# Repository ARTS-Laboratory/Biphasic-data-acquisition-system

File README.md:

# Biphasic-data-acquisition-system
Data acquisition system for the biphasic measurement of multifunctional materials. The measurement method is described in by Downey et al [1], while the initial layout of the hardware was developed by Hasan Borke Birgin at the University of Perugia. Figure 1 shows an overview of the bi-phasic measurement approach. 

<p align="center">
Figure 2: The Biphasic DC measurement approach, showing: (left) electrical signals of a 1 Hz square wave: sensing current with 50% duty cycle showing the discharge and measure regions, as well as the sample points for the applied and sense voltages, and; (right) time-based comparison of traditional DC resistance and the proposed biphasic DC measurement method using a 50% duty cycle and 9 varying sensing current frequencies, annotated on the right-hand side of the figure. 
</p>

[1] Austin Downey, Antonella D'Alessandro, Filippo Ubertini, Simon Laflamme and Randall Geiger. Biphasic DC Measurement Approach for Enhanced Measurement Stability and Multi-channel Sampling of Self-sensing Multi-functional Structural Materials Doped With Carbon-based Additives. Smart Materials and Structures, vol. 26, no. 6, 2017, p. 065008. doi:10.1088/1361-665X/aa6b66

## DAQ Design
1. This contains the hardware design and code for the DAQ system
1. Orginized by versions

## Licensing and Citation

[![CC BY-SA 4.0][cc-by-sa-shield]][cc-by-sa]

This work is licensed under a
[Creative Commons Attribution-ShareAlike 4.0 International License][cc-by-sa].

[cc-by-sa]: http://creativecommons.org/licenses/by-sa/4.0/
[cc-by-sa-image]: https://licensebuttons.net/l/by-sa/4.0/88x31.png
[cc-by-sa-shield]: https://img.shields.io/badge/License-CC%20BY--SA%204.0-lightgrey.svg

Cite as:

ARTS-Lab. Biphasic data acquisition system. GitHub. URL: https://github.com/ARTS-Laboratory/Biphasic-data-acquisition-system
 
in bibtex

@Misc{ARTSLabBiphasicDataAcquisition,   
  author       = {{ARTS-L}ab},  
  howpublished = {GitHub},  
  title        = {Biphasic Data Acquisition System},   
  groups       = {{ARTS-L}ab},  
  url          = {https://github.com/ARTS-Laboratory/Biphasic-data-acquisition-system},  
  note  = {Accessed: Month dd, yyyy},   
}

<p align="center">
QR code for repo.
</p>

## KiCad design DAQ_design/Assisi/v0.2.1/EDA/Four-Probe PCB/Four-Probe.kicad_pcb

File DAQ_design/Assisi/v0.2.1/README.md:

# Assisi V0.2.1

* This uses kicad-9.0.5 -->  https://downloads.kicad.org/kicad/windows/explore/stable/download/kicad-9.0.5-x86_64.exe
* Use a NI-9221 with a DSUB 25 female 
	* https://www.digikey.com/en/products/detail/amphenol-cs-fci/D25S33E4PA00LF/1538080
	* https://www.digikey.com/en/products/detail/edac-inc/630-025-640-541/10867386

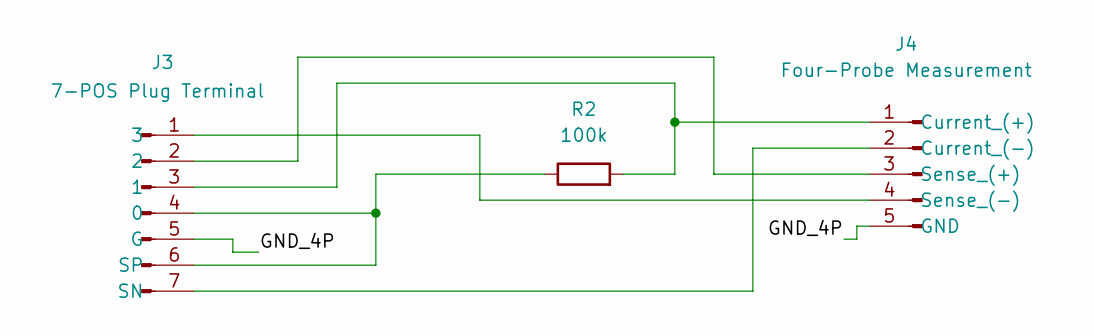
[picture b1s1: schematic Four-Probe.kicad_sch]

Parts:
J3: 7-POS Plug Terminal; PHOENIX_1786459
J4: Four-Probe Measurement; PhoenixContact_MSTBA_2,5_5-G-5,08_1x05_P5.08mm_Horizontal
R2: 100k; R_Axial_DIN0207_L6.3mm_D2.5mm_P10.16mm_Horizontal

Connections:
/GND_4P: J3.5 (G), J4.5 (GND)
unnamed: J3.4 (0), J3.6 (SP), R2.1
unnamed: J3.3 (1), J4.1 (Current_(+)), R2.2
unnamed: J3.1 (3), J4.4 (Sense_(-))
unnamed: J3.7 (SN), J4.2 (Current_(-))
unnamed: J3.2, J4.3 (Sense_(+))

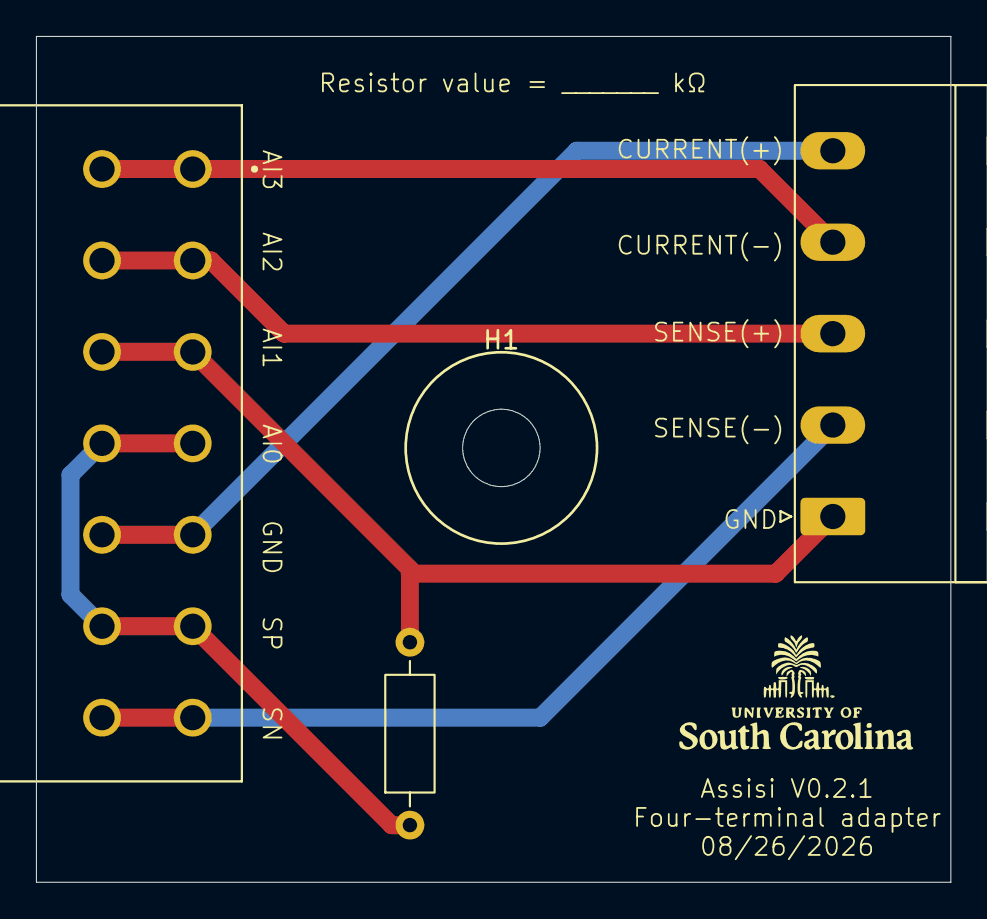
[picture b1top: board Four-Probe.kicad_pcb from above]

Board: 2 copper layers, 50.8 x 47.0 mm, 5 parts (0 on the bottom side), 6 nets.

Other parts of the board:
G2: LOGO; uofsc
H1: MountingHole_Pad; MountingHole_4.3mm_M4

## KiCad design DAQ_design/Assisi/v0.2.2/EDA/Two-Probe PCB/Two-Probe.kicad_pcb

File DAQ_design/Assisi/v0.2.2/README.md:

# Assisi V0.2.2

* This uses kicad-9.0.5 -->  https://downloads.kicad.org/kicad/windows/explore/stable/download/kicad-9.0.5-x86_64.exe
* Update from PCB version 0.2.1 to 0.2.2.
* Add a notch/cutout in the PCB so the board fits in the enclosure more cleanly.
* Shorten the PCB slightly to reduce package size.
* Continue using external power supplies.
* Target 9 V external power as the preferred operating supply.
* Explore 7 V external power as an alternate option.
* Clean up the PCB schematic for readability and consistency.
* Clean up PCB traces and routing.
* Update the enclosure mounting pattern from three holes to two holes.

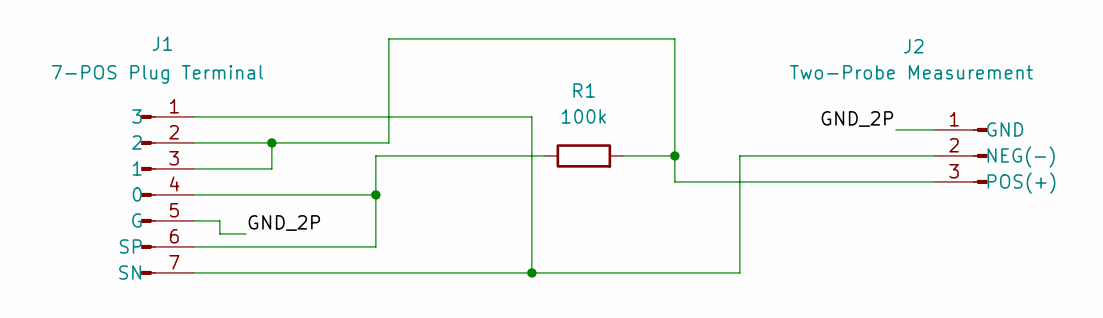
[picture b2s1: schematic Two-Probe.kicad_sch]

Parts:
J1: 7-POS Plug Terminal; PHOENIX_1786459
J2: Two-Probe Measurement; PhoenixContact_MSTBA_2,5_3-G-5,08_1x03_P5.08mm_Horizontal
R1: 100k; R_Axial_DIN0207_L6.3mm_D2.5mm_P10.16mm_Horizontal

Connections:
/GND_2P: J1.5 (G), J2.1 (GND)
unnamed: J1.4 (0), J1.6 (SP), R1.1
unnamed: J1.2, J1.3 (1), J2.3 (POS(+)), R1.2
unnamed: J1.1 (3), J1.7 (SN), J2.2 (NEG(-))

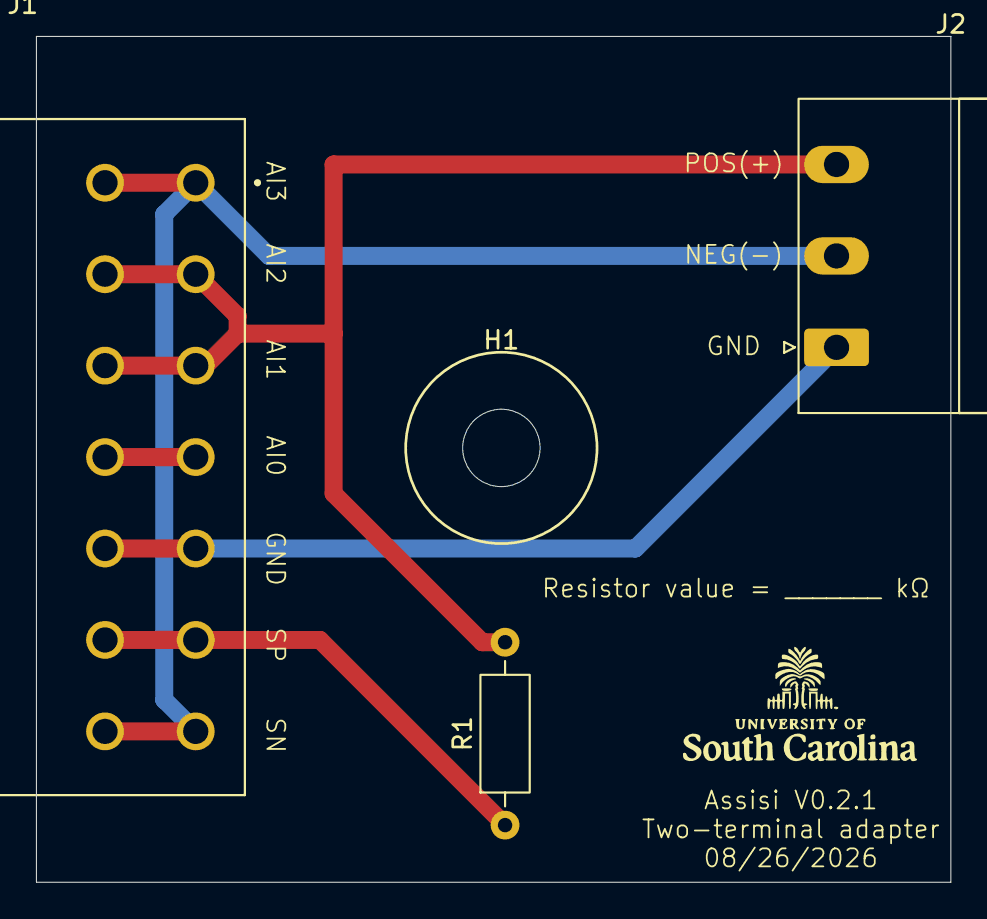
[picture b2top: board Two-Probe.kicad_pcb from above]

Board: 2 copper layers, 50.8 x 47.0 mm, 5 parts (0 on the bottom side), 4 nets.

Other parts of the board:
G2: LOGO; uofsc
H1: MountingHole_Pad; MountingHole_4.3mm_M4

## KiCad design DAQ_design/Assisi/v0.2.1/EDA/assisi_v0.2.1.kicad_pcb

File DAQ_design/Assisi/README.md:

# Assisi
* Biphasic DAQ with ADC done cDAQ hardware

## V0.1.0
* Initial Assisi PCB version copied forward from earlier circuitry.
* Used as a holdover design to preserve and test the core circuit layout.

## V0.2.0
* First version focused on adapting the DAQ PCB for the enclosure.
* Began moving the design toward a boxed, deployable hardware package.

## V0.2.1
* Fixed issues found in V0.2.0 and added enclosure bolt holes.
* Printed enclosure version sent to Italy in June 2026.

## V0.2.2
* Shortened the PCB and added a notch/cutout for better enclosure fit.
* Cleaned up the schematic, PCB traces, and moved to two mounting holes.

## V0.2.3
* Future version to explore direct 5 V power input without the Arduino regulator.
* Planned update to include integrated resistor management.

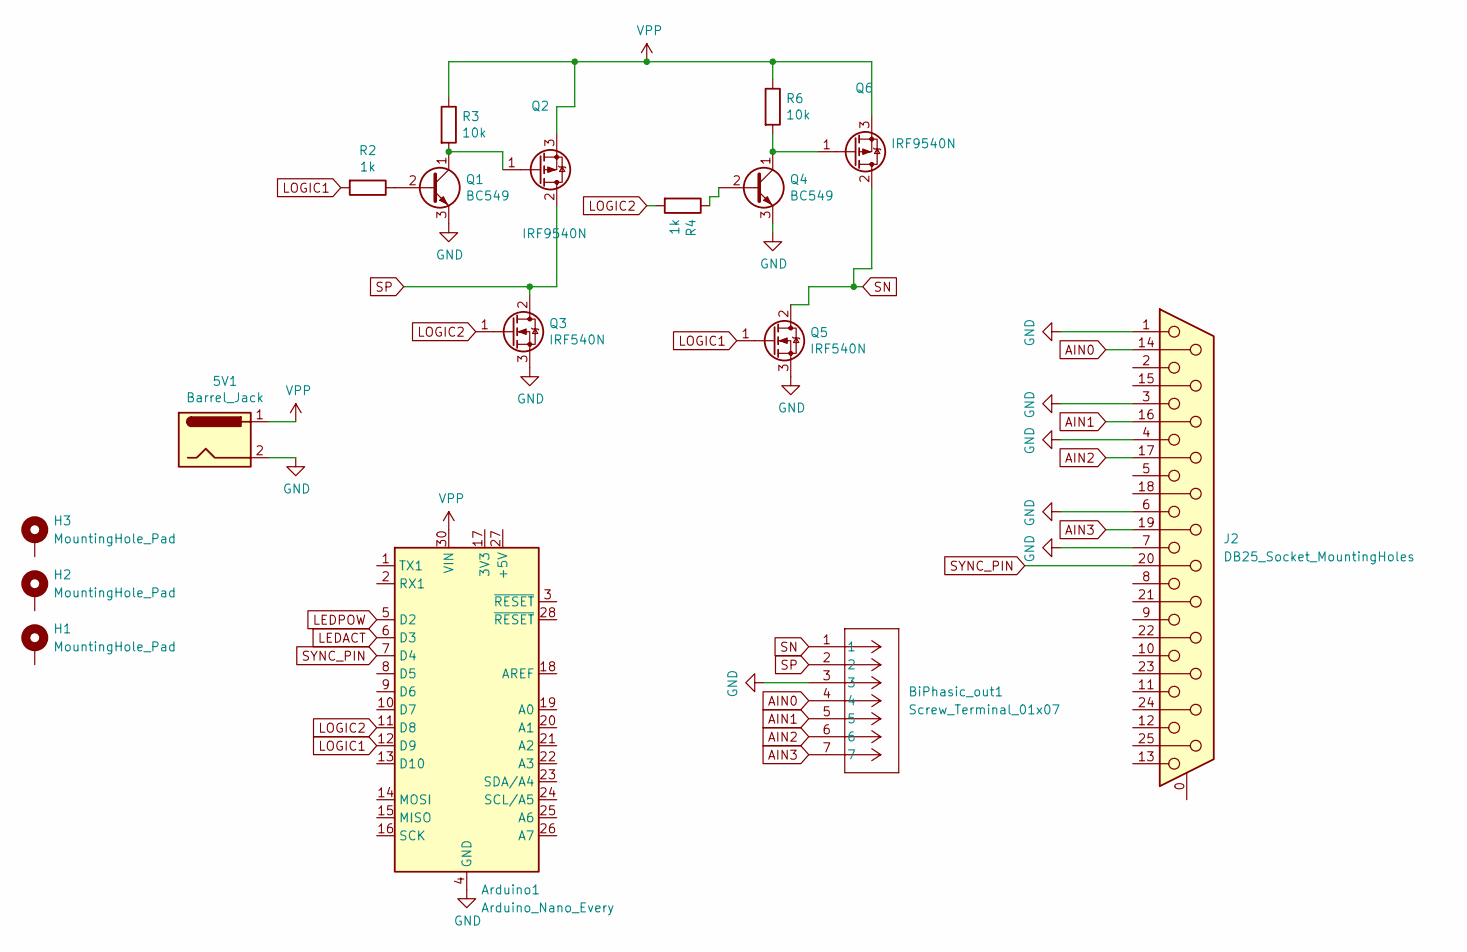
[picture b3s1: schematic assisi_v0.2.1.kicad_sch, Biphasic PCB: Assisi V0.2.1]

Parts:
5V1: Barrel_Jack; BarrelJack_Horizontal
Arduino1: Arduino_Nano_Every; Arduino_Nano
BiPhasic_out1: Screw_Terminal_01x07; CONN7_57297_PXC
H1, H2, H3: MountingHole_Pad; MountingHole_4.3mm_M4
J2: DB25_Socket_MountingHoles; DSUB-25_Pins_Horizontal_P2.77x2.84mm_EdgePinOffset7.70mm_Ho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
Q1, Q4: BC549; TO-92_Inline_Wide
Q2, Q6: IRF9540N; TO-220-3_Vertical
Q3, Q5: IRF540N; TO-220-3_Vertical
R2, R4: 1k; R_1206_3216Metric
R3, R6: 10k; R_1206_3216Metric

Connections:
AIN0: BiPhasic_out1.4, J2.14
AIN1: BiPhasic_out1.5, J2.16
AIN2: BiPhasic_out1.6, J2.17
AIN3: BiPhasic_out1.7, J2.19
GND: 5V1.2, Arduino1.4 (GND), Arduino1.29 (GND), BiPhasic_out1.3, J2.1, J2.3, J2.4, J2.6, J2.7, Q1.3 (E), Q3.3 (S), Q4.3 (E), Q5.3 (S); also elsewhere on the board
LEDACT: Arduino1.6 (D3)
LEDPOW: Arduino1.5 (D2)
LOGIC1: Arduino1.12 (D9), Q5.1 (G), R2.2
LOGIC2: Arduino1.11 (D8), Q3.1 (G), R4.2
unnamed: Q1.2 (B), R2.1
unnamed: Q1.1 (C), Q2.1 (G), R3.2
unnamed: Q4.2 (B), R4.1
unnamed: Q4.1 (C), Q6.1 (G), R6.2
SN: BiPhasic_out1.1, Q5.2 (D), Q6.2 (D)
SP: BiPhasic_out1.2, Q2.2 (D), Q3.2 (D)
SYNC_PIN: Arduino1.7 (D4), J2.20
VPP: 5V1.1, Arduino1.30 (VIN), Q2.3 (S), Q6.3 (S), R3.1, R6.1; also elsewhere on the board

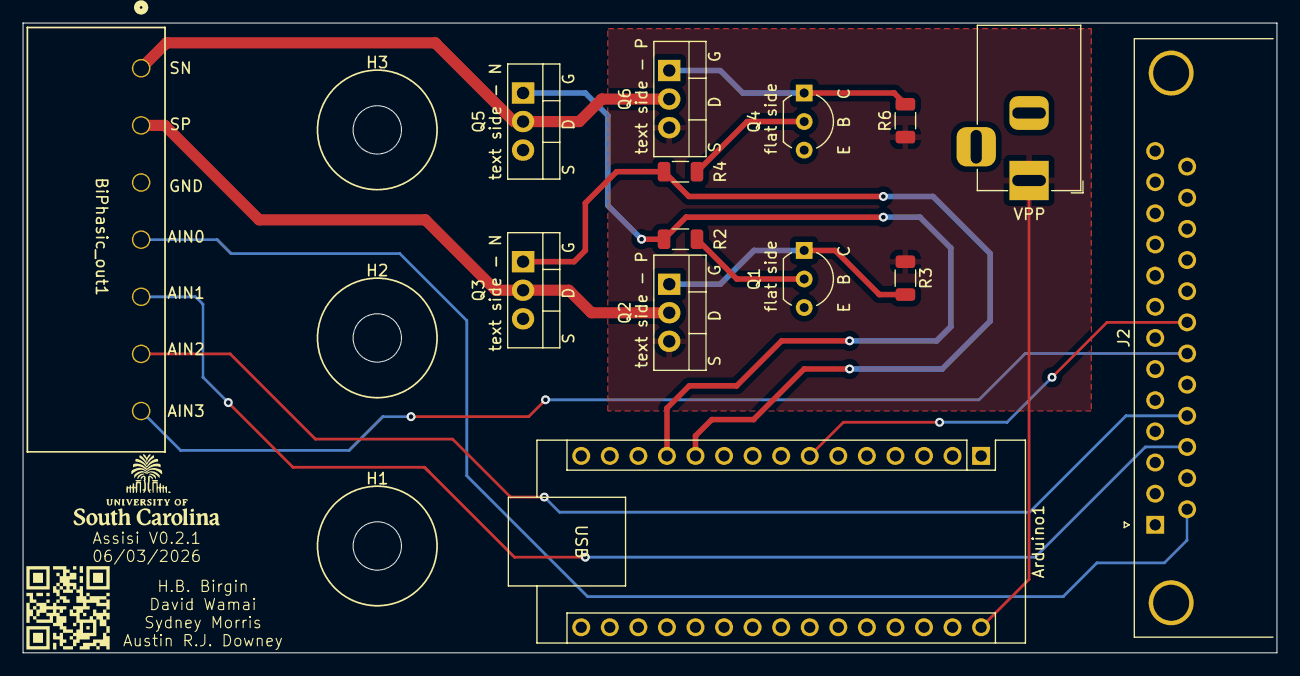
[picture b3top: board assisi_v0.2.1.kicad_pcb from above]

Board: 2 copper layers, 111.5 x 56.0 mm, 19 parts (0 on the bottom side), 15 nets.

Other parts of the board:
G2: LOGO; uofsc
G7: LOGO; github
VPP: Barrel_Jack; BarrelJack_Horizontal

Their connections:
GND: VPP.2; also elsewhere on the board
VPP: VPP.1; also elsewhere on the board

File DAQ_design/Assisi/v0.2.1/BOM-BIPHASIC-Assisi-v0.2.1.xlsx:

Designator | Component | MFR Part Number | Amount in Inventory | Amount Per Board | Individual Cost | Total Cost | Notes | Vendor 1 | Vendor 2 | Vendor 3 | Vendor 4 | Vendor 5 | Vendor 6
VPP | Barrel Jack | PJ-002A | 6 | 1 | 0.57999999999999996 | 0.57999999999999996 |  | PJ-002A Same Sky (Formerly CUI Devices) | Power Connectors | DigiKey
Arduino1 | Arduino Nano Microcontroller |  | 0 | 1 | 5.9 | 5.9 | Can be swapped with a nano every for a higher ram option | https://www.digikey.com/en/products/detail/dfrobot/DFR0010/6588448
BiPhasic_out1 | Screw Terminal Male | 1757064 | 2 | 1 | 4.72 | 4.72 | Allow for secure yet detachable wiring | 1757297 Phoenix Contact | Headers, Plugs and Sockets | DigiKey
BiPhasic_out1 | Screw Terminal Female | 1757297 | 7 | 1 | 12.55 | 12.55 | Allow for secure yet detachable wiring | 1757064 Phoenix Contact | Headers, Plugs and Sockets | DigiKey
BiPhasic_out1 | Screw Terminal Female with strain relief | 1776113 | 2 | 1 | 9.5 | 9.5 | Allow for secure yet detachable wiring (with strain relief) | https://www.digikey.com/en/products/detail/phoenix-contact/1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
J2 DSUB | DSUB-25 Female Connector | D25S33E4GX00LF | 3 | 1 | 1.81 | 1.81 | Connect to NI 9221 | https://www.digikey.com/en/products/detail/amphenol-cs-fci/D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
R2, R4 | 1k Ohm Resistor | RC1206FR-071KL | 42 | 2 | 0.1 | 0.2 | Or use resistor book: https://www.adafruit.com/product/441 | RC1206FR-071KL YAGEO | Chip Resistor - Surface Mount | DigiKey
R3, R6 | 10k Ohm Resistor | RMCF1206FT10K0 | 42 | 2 | 0.1 | 0.2 | Or use resistor book: https://www.adafruit.com/product/442 | RMCF1206FT10K0 Stackpole Electronics Inc | Chip Resistor - Surface Mount | Digi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
Q1, Q4 | Epitaxial Silicon Transistor | BC550CTA | 4 | 2 | 0.28000000000000003 | 0.56000000000000005 | CTA is higher-gain, low-noise | BC550CTA onsemi | Single Bipolar Transistors | DigiKey
Q2, Q6 | HEXFET power MOSFET | IRF9540NPBF | 0 | 2 | 2.0699999999999998 | 4.1399999999999997 | Need both for complementary pair. P-channel (when gate is lower than source, pu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 | IRF9540NPBF Infineon Technologies | Single FETs, MOSFETs | DigiKey
Q3, Q5 | IRF540N HEXFET power MOSFET |  | 6 | 2 | 1.93 | 3.86 | Need both for complementary pair. N-channel (when gate is higher than source, p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 | IRF540NPBF Infineon Technologies | Single FETs, MOSFETs | DigiKey
H1, H2, H3 | M4 Flat Washer | M51420.040.0001 | 60 | 9 | 1.66E-2 | 0.14940000000000001 | Package quantity 50 | https://www.grainger.com/product/Flat-Washer-18-8-26WC32
 | M4 x 40 mm Socket Head Cap Screw | 6DB37 | 32 | 6 | 0.20620000000000002 | 1.2372000000000001 | Package quantity 50. secures box lid to bottom | https://www.grainger.com/product/Socket-Head-Cap-Screw-M4x0-6DB37
 | M4 x 16 mm Socket Head Cap Screw | 22UC47 | 41 | 3 | 0.11800000000000001 | 0.35400000000000004 | Package quantity 50. secures PCB to box bottom | https://www.grainger.com/product/Socket-Head-Cap-Screw-M4x0-22UC47
 | M4 Hex Nut | M51080.040.0001 | 60 | 9 | 1.54E-2 | 0.1386 | Package quantity 50 | https://www.grainger.com/product/Hex-Nut-Std-Hex-22UK82
 | DSUB Screw | 5746879-1 | 10 | 2 | 0.59 | 1.18 |  | 5746879-1 TE Connectivity AMP Connectors | D-Sub, D-Shaped Connector Jackscrews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
 | 15 Pos Female Header Pins |  | 0 | 2 | 5.86 | 11.72 | Solder to microcontroller footprint to make detachable | 1-215297-5 TE Connectivity AMP Connectors | Headers, Receptacles, Female Socket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
 | Power Supply 9V |  | 1 | 1 | 18.600000000000001 | 18.600000000000001 | Convenient and plugs into wall | GST60A12-P1J MEAN WELL USA Inc. | AC DC Desktop, Wall Power Adapters | DigiKey
 | Power Supply 12V |  | 3 | 1 | 18.600000000000001 | 18.600000000000001 | Convenient and plugs into wall | https://www.digikey.com/en/products/detail/mean-well-usa-inc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
 | hook up wire | 76502.18.01 | 1 | 1 | 65.510000000000005 | 65.510000000000005 | 500' of 18 AWG 16/30 hook-up wire, black, will be color-coded with crimp termin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 | https://www.digikey.com/en/products/detail/encore-wire/76502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
 | Ferrule - gray | 3200519 | 25 | 2 | 0.15 | 0.3 | Color coded Ferrule to go with the black wire | https://www.digikey.com/en/products/detail/phoenix-contact/3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
 | Ferrule - yellow | 3201097 | 21 | 2 | 0.15 | 0.3 | Color coded Ferrule to go with the black wire | https://www.digikey.com/en/products/detail/phoenix-contact/3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
 | Ferrule - white | 3201110 | 25 | 2 | 0.15 | 0.3 | Color coded Ferrule to go with the black wire | https://www.digikey.com/en/products/detail/phoenix-contact/3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
 | Ferrule - red | 3200904 | 25 | 2 | 0.15 | 0.3 | Color coded Ferrule to go with the black wire | https://www.digikey.com/en/products/detail/phoenix-contact/3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
wire to mesh connector | Barrier Terminal Strip | 6YH99 |  | 1 | 0.45083333333333336 | 0.45083333333333336 | Cut apart and use to connect to wire mesh in concrete | https://www.grainger.com/product/Barrier-Terminal-Strip-12-6YH99
 | cDAQ NI 9221 with DSUB | NI 9221 779373-01 | 3 | 1 | 1220 | 1220 |  | NI-9221 - NI
 | cDAQ Chassis NI 9171 | NI 9171 781425-01 | 3 | 1 | 548 | 548
 |  |  |  |  | Total | 1931.1600333333333

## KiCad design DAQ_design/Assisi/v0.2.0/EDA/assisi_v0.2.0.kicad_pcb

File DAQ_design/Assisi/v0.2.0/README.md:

# Assisi V0.2.0

* This uses kicad-9.0.5 -->  https://downloads.kicad.org/kicad/windows/explore/stable/download/kicad-9.0.5-x86_64.exe
* Use a NI-9221 wiht a DSUB 25 female 
	* https://www.digikey.com/en/products/detail/amphenol-cs-fci/D25S33E4PA00LF/1538080
	* https://www.digikey.com/en/products/detail/edac-inc/630-025-640-541/10867386

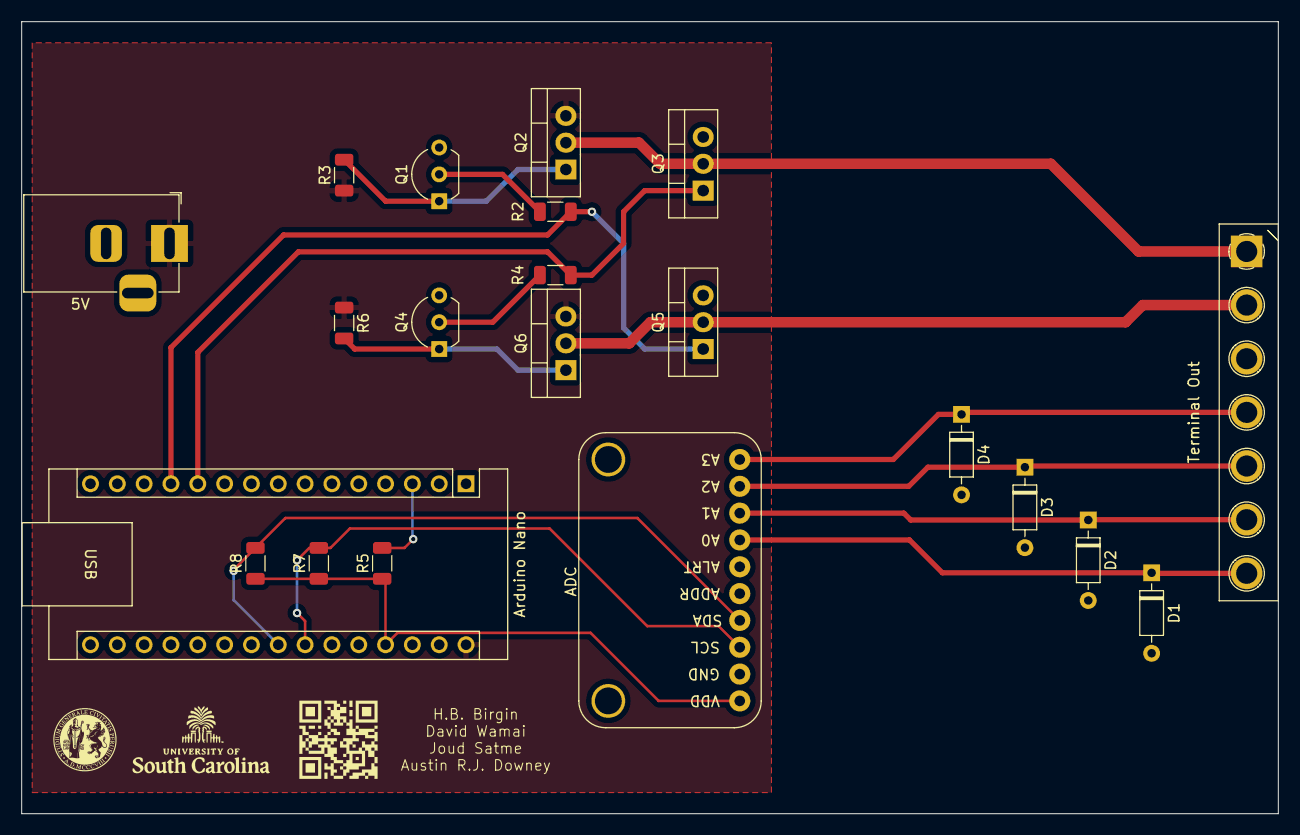
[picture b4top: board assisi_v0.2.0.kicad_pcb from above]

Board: 2 copper layers, 119.0 x 75.0 mm, 25 parts (1 on the bottom side), 18 nets.

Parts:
5V: Barrel_Jack; BarrelJack_Horizontal
ADC: ADS1115IDGS; Adafruit_ADS1115
Arduino Nano: Arduino_Nano_Every; Arduino_Nano
D1, D2, D3, D4: D_Zener; D_DO-35_SOD27_P7.62mm_Horizontal
G2: LOGO; uofsc
G3: LOGO; upg
G5: LOGO; schematic
G7: LOGO; github
Q1, Q4: BC549; TO-92_Inline_Wide
Q2, Q6: IRF9540N; TO-220-3_Vertical
Q3, Q5: IRF540N; TO-220-3_Vertical
R2, R4: 1k; R_1206_3216Metric
R3, R5, R6, R7, R8: 10k; R_1206_3216Metric
Terminal Out: Screw_Terminal_01x07; TerminalBlock_Phoenix_MKDS-1,5-7-5.08_1x07_P5.08mm_Horizont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

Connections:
AIN0: ADC.7 (AIN0), D1.1 (K), Terminal Out.7
AIN1: ADC.8 (AIN1), D2.1 (K), Terminal Out.6
AIN2: ADC.9 (AIN2), D3.1 (K), Terminal Out.5
AIN3: ADC.10 (AIN3), D4.1 (K), Terminal Out.4
GND: 5V.2, ADC.2 (GND), ADC.5 (ADDR), Arduino Nano.4 (GND), Arduino Nano.29 (GND), D1.2 (A), D2.2 (A), D3.2 (A), D4.2 (A), Q1.3 (E), Q3.3 (S), Q4.3 (E), Q5.3 (S), Terminal Out.3
LOGIC1: Arduino Nano.12 (D9), Q5.1 (G), R2.2
LOGIC2: Arduino Nano.11 (D8), Q3.1 (G), R4.2
unnamed: ADC.3 (SCL), Arduino Nano.24 (SCL/A5), R7.2
unnamed: ADC.4 (SDA), Arduino Nano.23 (SDA/A4), R8.2
unnamed: Arduino Nano.3 (~RESET), R5.2
unnamed: Q1.2 (B), R2.1
unnamed: Q1.1 (C), Q2.1 (G), R3.2
unnamed: Q4.2 (B), R4.1
unnamed: Q4.1 (C), Q6.1 (G), R6.2
SN: Q5.2 (D), Q6.2 (D), Terminal Out.2
SP: Q2.2 (D), Q3.2 (D), Terminal Out.1
VDD: ADC.1 (VDD), Arduino Nano.27 (+5V), R5.1, R7.1, R8.1
VPP: 5V.1, Arduino Nano.30 (VIN), Q2.3 (S), Q6.3 (S), R3.1, R6.1

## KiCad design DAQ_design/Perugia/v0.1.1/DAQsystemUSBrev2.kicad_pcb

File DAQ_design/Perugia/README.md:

# Perugia
* Biphasic DAQ with ADC done on an embedded microcontroller

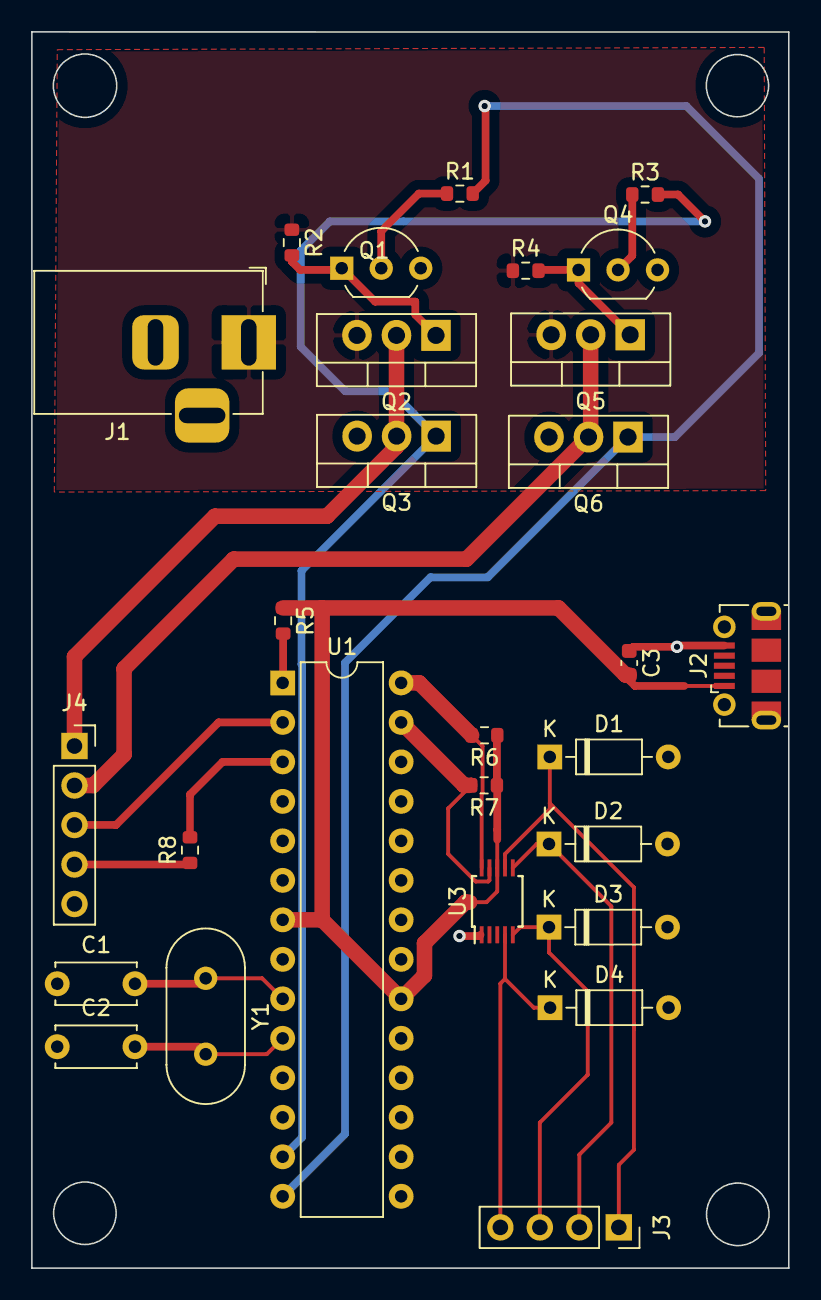
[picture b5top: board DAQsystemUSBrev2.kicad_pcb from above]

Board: 2 copper layers, 48.7 x 79.5 mm, 28 parts (0 on the bottom side), 23 nets.

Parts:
C1, C2: 22uF; C_Disc_D5.0mm_W2.5mm_P5.00mm
C3: 100nF; C_0603_1608Metric
D1, D2, D3, D4: D_Zener; D_DO-35_SOD27_P7.62mm_Horizontal
J1: Barrel_Jack; BarrelJack_Horizontal
J2: USB_B_Micro; USB_Micro-B_Molex-105017-0001
J3: Conn_01x04_Female; PinSocket_1x04_P2.54mm_Vertical
J4: Conn_01x05_Female; PinSocket_1x05_P2.54mm_Vertical
Q1, Q4: BC549; TO-92_Inline_Wide
Q2, Q5: IRF9540N; TO-220-3_Vertical
Q3, Q6: IRF540N; TO-220-3_Vertical
R1, R3, R8: 1k; R_0603_1608Metric
R2, R4, R5, R6, R7: 10k; R_0603_1608Metric
U1: ATmega328-PU; DIP-28_W7.62mm
U3: ADS1115IDGS; TSSOP-10_3x3mm_P0.5mm
Y1: 16MHz; Crystal_HC49-U_Vertical

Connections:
AIN0: D4.1, J3.4, U3.4
AIN1: D3.1, J3.3, U3.5
AIN2: D2.1, J3.2, U3.6
AIN3: D1.1, J3.1, U3.7
GND: C1.1, C2.1, C3.1, D1.2, D2.2, D3.2, D4.2, J1.2, J2.5, J4.5, Q1.3, Q3.3, Q4.3, Q6.3, U1.8, U1.22, U3.1
LOGIC1: Q6.1, R1.2, U1.14
LOGIC2: Q3.1, R3.2, U1.13
unnamed: C1.2, U1.9, Y1.1
unnamed: C2.2, U1.10, Y1.2
unnamed: J4.4, R8.1
unnamed: Q1.1, Q2.1, R2.2
unnamed: Q1.2, R1.1
unnamed: Q4.1, Q5.1, R4.2
unnamed: Q4.2, R3.1
unnamed: R5.2, U1.1
unnamed: R6.2, U1.28, U3.10
unnamed: R7.2, U1.27, U3.9
RX: J4.3, U1.2
SN: J4.2, Q5.2, Q6.2
SP: J4.1, Q2.2, Q3.2
TX: R8.2, U1.3
VDD: C3.2, J2.1, R5.1, R6.1, R7.1, U1.7, U1.20, U3.8
VPP: J1.1, Q2.3, Q5.3, R2.1, R4.1

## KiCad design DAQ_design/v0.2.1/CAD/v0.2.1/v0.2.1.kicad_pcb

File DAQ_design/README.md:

# DAQ Design
Hardware design and code for the DAQ system. Hardware variations are named after cities in central Italy. 

## Perugia
* Biphasic DAQ with ADC done on an embedded microcontroller

<p align="center">

## Assisi
* Biphasic DAQ with ADC done using cDAQ hardware

<p align="center">

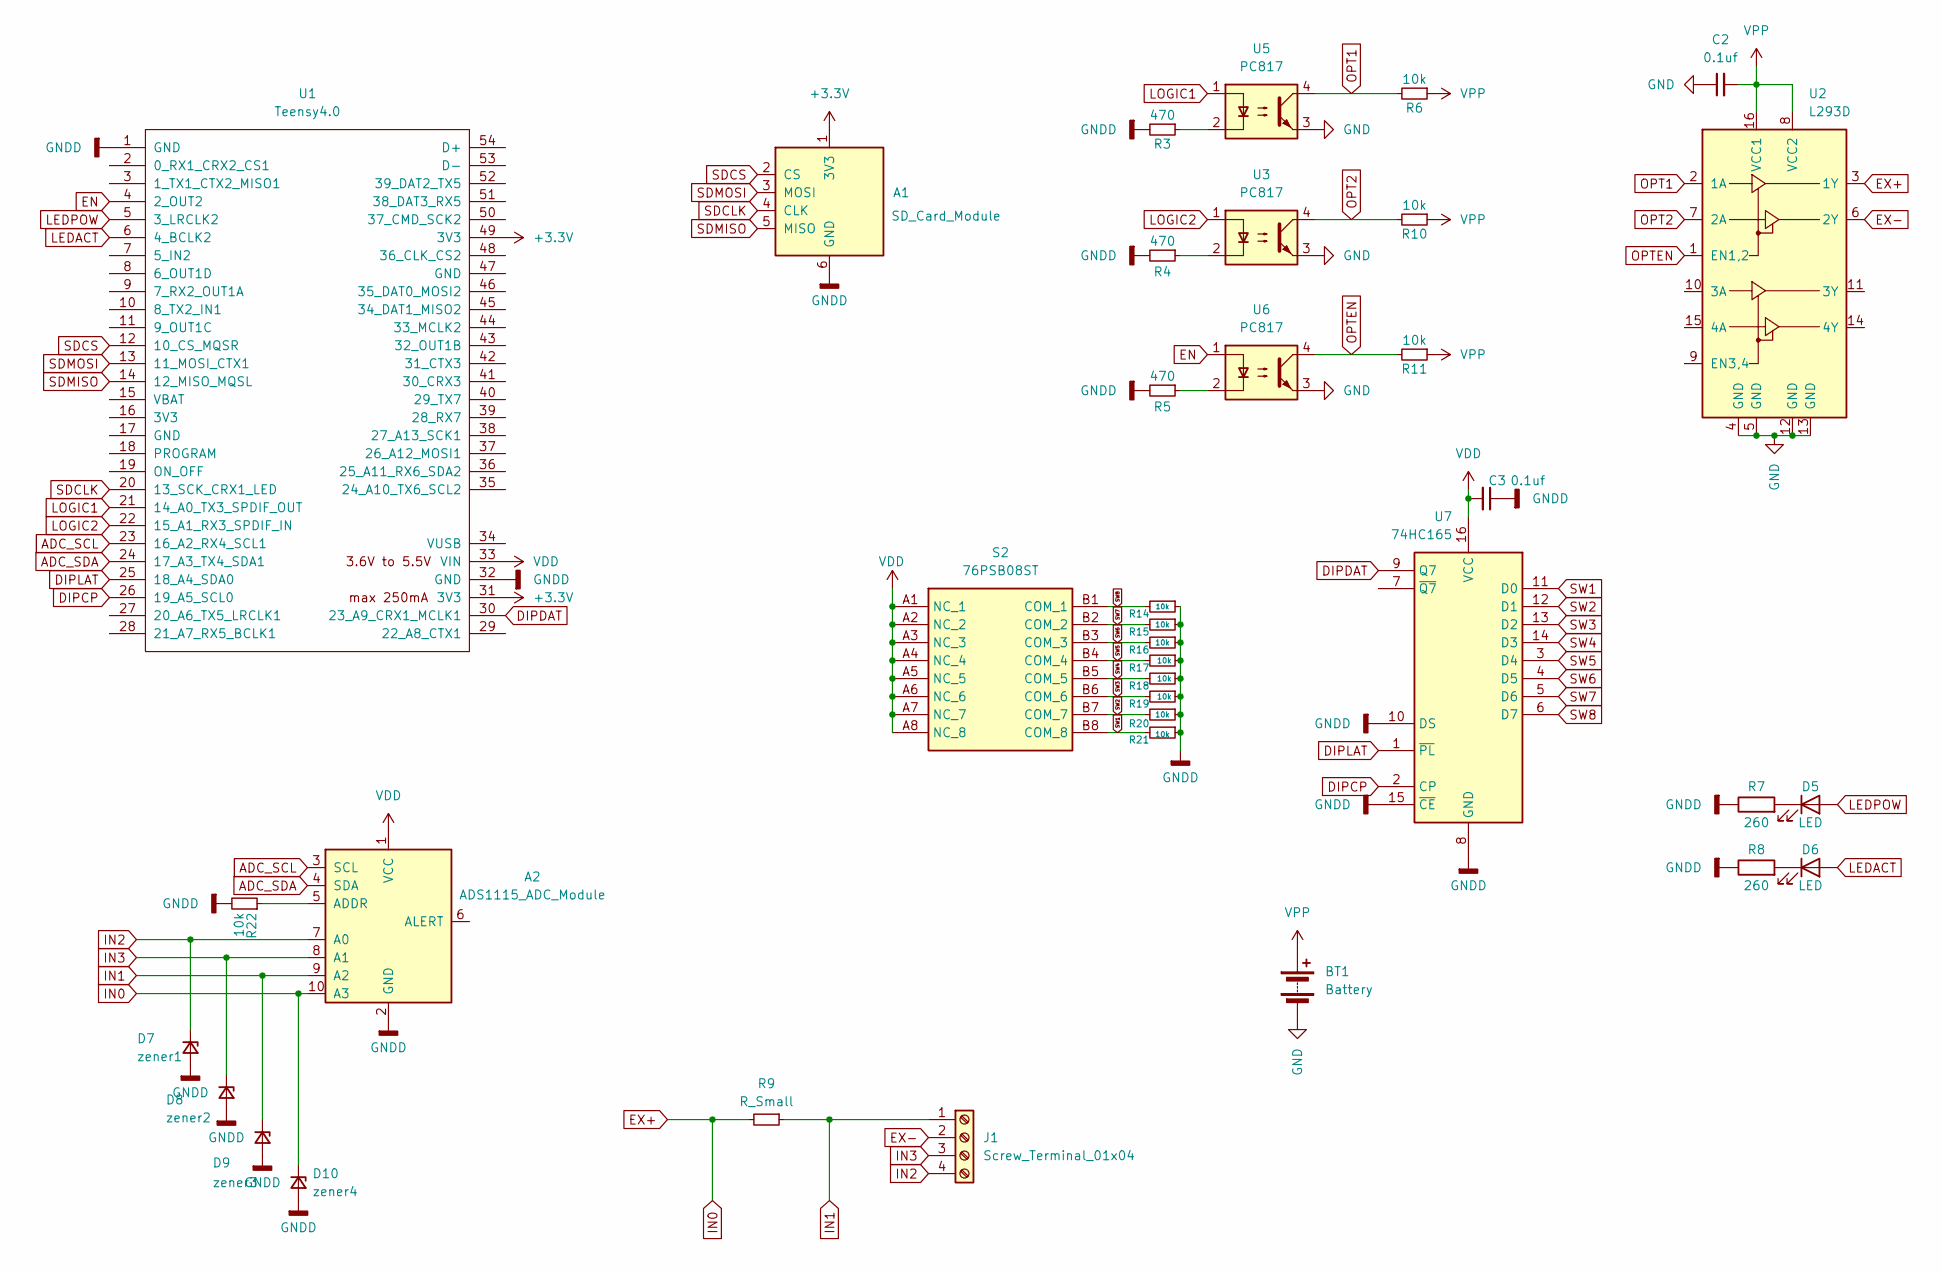
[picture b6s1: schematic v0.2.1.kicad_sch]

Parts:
A1: SD_Card_Module
A2: ADS1115_ADC_Module; ADC1115_ADC_Module
BT1: Battery; JST_GH_SM02B-GHS-TB_1x02-1MP_P1.25mm_Horizontal
C2, C3: 0.1uf; C_1206_3216Metric
D5, D6: LED; LED_1206_3216Metric_Pad1.42x1.75mm_HandSolder
D7: zener1; D_1206_3216Metric_Pad1.42x1.75mm_HandSolder
D8: zener2; D_1206_3216Metric_Pad1.42x1.75mm_HandSolder
D9: zener3; D_1206_3216Metric_Pad1.42x1.75mm_HandSolder
D10: zener4; D_1206_3216Metric_Pad1.42x1.75mm_HandSolder
J1: Screw_Terminal_01x04; TerminalBlock_bornier-4_P5.08mm
R3, R4, R5: 470; R_1206_3216Metric
R6, R10, R11: 10k; R_1206_3216Metric
R7, R8: 260; R_1206_3216Metric
R9: R_Small; R_Axial_DIN0204_L3.6mm_D1.6mm_P7.62mm_Horizontal
R14, R15, R16, R17, R18, R19, R20, R21, R22: 10k; R_0805_2012Metric
S2: 76PSB08ST; Manufacturer_Part_Number 76PSB08ST; Mouser Part Number 706-76PSB08ST
U1: Teensy4.0; Teensy40
U2: L293D; DIP-16_W7.62mm
U3, U5, U6: PC817; DIP-4_W7.62mm
U7: 74HC165; DIP-16_W7.62mm

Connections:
+3.3V: A1.1 (3V3), U1.31 (3V3), U1.49 (3V3)
ADC_SCL: A2.3 (SCL), U1.23 (16_A2_RX4_SCL1)
ADC_SDA: A2.4 (SDA), U1.24 (17_A3_TX4_SDA1)
DIPCP: U1.26 (19_A5_SCL0), U7.2 (CP)
DIPDAT: U1.30 (23_A9_CRX1_MCLK1), U7.9 (Q7)
DIPLAT: U1.25 (18_A4_SDA0), U7.1 (~PL)
EN: U1.4 (2_OUT2), U6.1
EX+: A2.10 (A3), D10.1 (K), R9.2, U2.3 (1Y)
EX-: J1.2, U2.6 (2Y)
GND: BT1.2 (-), C2.1, U2.4 (GND), U2.5 (GND), U2.12 (GND), U2.13 (GND), U3.3, U5.3, U6.3
GNDD: A1.6 (GND), A2.2 (GND), C3.1, D7.2 (A), D8.2 (A), D9.2 (A), D10.2 (A), R3.2, R4.2, R5.2, R7.1, R8.1, R14.1, R15.1, R16.1, R17.1, R18.1, R19.1, R20.1, R21.1, R22.2, U1.1 (GND), U1.32 (GND), U7.8 (GND), U7.10 (DS), U7.15 (~CE)
IN1: A2.9 (A2), D9.1 (K), J1.1, R9.1
IN2: A2.7 (A0), D7.1 (K), J1.4
IN3: A2.8 (A1), D8.1 (K), J1.3
LEDACT: D6.2 (A), U1.6 (4_BCLK2)
LEDPOW: D5.2 (A), U1.5 (3_LRCLK2)
LOGIC1: U1.21 (14_A0_TX3_SPDIF_OUT), U5.1
LOGIC2: U1.22 (15_A1_RX3_SPDIF_IN), U3.1
unnamed: A2.5 (ADDR), R22.1
unnamed: D5.1 (K), R7.2
unnamed: D6.1 (K), R8.2
unnamed: R3.1, U5.2
unnamed: R4.1, U3.2
unnamed: R5.1, U6.2
OPT1: R6.2, U2.2 (1A), U5.4
OPT2: R10.2, U2.7 (2A), U3.4
OPTEN: R11.2, U2.1 (EN1,2), U6.4
SDCLK: A1.4 (CLK), U1.20 (13_SCK_CRX1_LED)
SDCS: A1.2 (CS), U1.12 (10_CS_MQSR)
SDMISO: A1.5 (MISO), U1.14 (12_MISO_MQSL)
SDMOSI: A1.3 (MOSI), U1.13 (11_MOSI_CTX1)
SW1: R21.2, S2.B8 (COM_8), U7.11 (D0)
SW2: R20.2, S2.B7 (COM_7), U7.12 (D1)
SW3: R19.2, S2.B6 (COM_6), U7.13 (D2)
SW4: R18.2, S2.B5 (COM_5), U7.14 (D3)
SW5: R17.2, S2.B4 (COM_4), U7.3 (D4)
SW6: R16.2, S2.B3 (COM_3), U7.4 (D5)
SW7: R15.2, S2.B2 (COM_2), U7.5 (D6)
SW8: R14.2, S2.B1 (COM_1), U7.6 (D7)
VDD: A2.1 (VCC), C3.2, S2.A1 (NC_1), S2.A2 (NC_2), S2.A3 (NC_3), S2.A4 (NC_4), S2.A5 (NC_5), S2.A6 (NC_6), S2.A7 (NC_7), S2.A8 (NC_8), U1.33 (VIN), U7.16 (VCC)
VPP: BT1.1 (+), C2.2, R6.1, R10.1, R11.1, U2.8 (VCC2), U2.16 (VCC1)

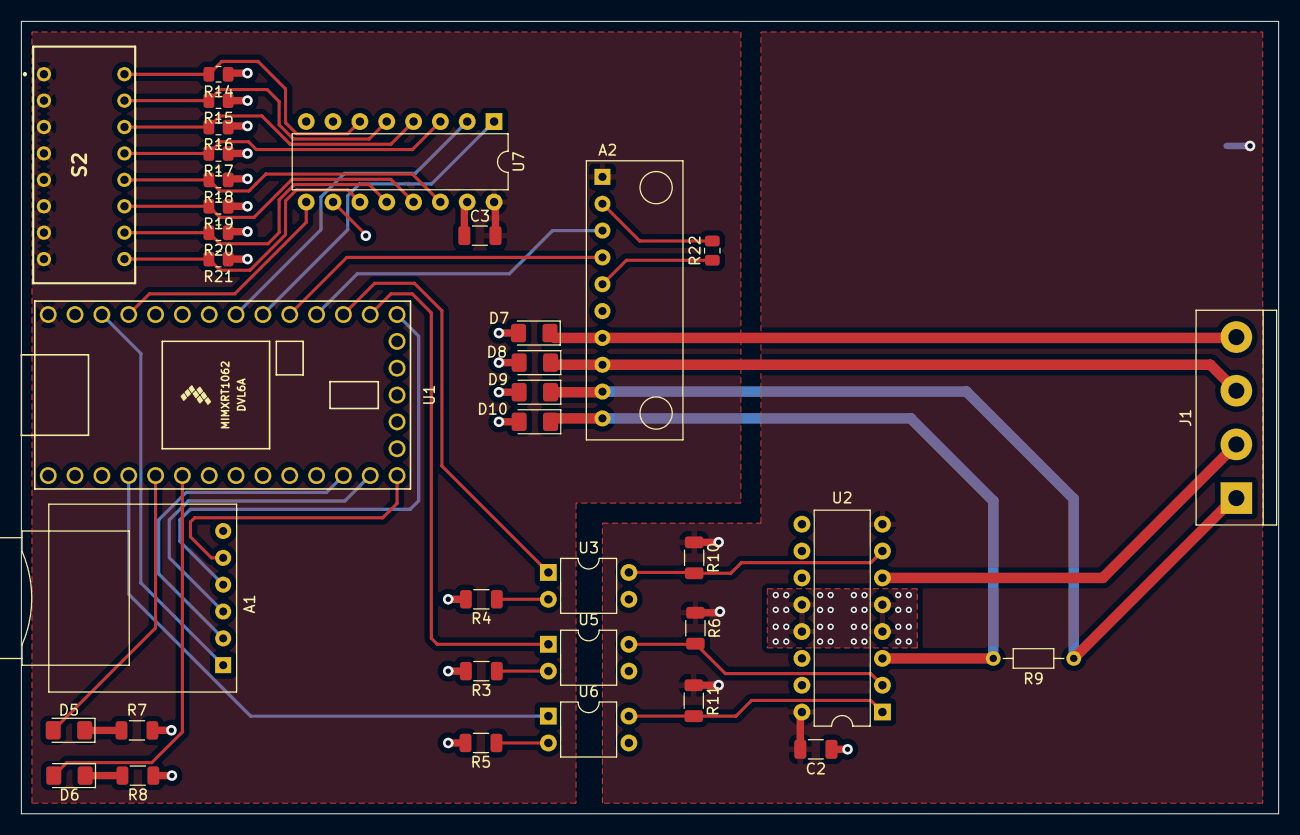
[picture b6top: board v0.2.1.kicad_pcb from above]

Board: 4 copper layers, 119.0 x 75.0 mm, 37 parts (1 on the bottom side), 41 nets.

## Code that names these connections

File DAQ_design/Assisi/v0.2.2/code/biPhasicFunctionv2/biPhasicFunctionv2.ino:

#include <Arduino.h>

#define LOGIC1 9 
#define LOGIC2 8
#define SYNC_PIN 4 // optional marker to NI side

unsigned long start_time = 0;
float userfrq = 1;
float period = 1;

// ISR Flag
volatile bool toggle_flag = false;

// Logic flag
bool L_state = false;
bool readchk = false;
unsigned long high_state_start_time = 0;
unsigned long high_state_duration = 0;

void setup(){
  Serial.begin(115200);

  pinMode(LOGIC1, OUTPUT);
  pinMode(LOGIC2, OUTPUT);
  pinMode(SYNC_PIN, OUTPUT);

  digitalWrite(LOGIC1, LOW);
  digitalWrite(LOGIC2, LOW);
  digitalWrite(SYNC_PIN, LOW);

  //Serial.println("Enter frequency in Hz (1, 2, 5, 10, 20, 50, 100):");
  //while (!Serial.available());

//  userfrq = Serial.parseFloat(); // Read requested period from user input
//  Serial.print("frequency set to: ");
//  Serial.println(userfrq);

float userfrq = 1.0; // presetting freq so i dont have to plug in usb

unsigned long start = millis();

while (!Serial.available() && millis() - start < 3000) {
}

if (Serial.available()) {
    userfrq = Serial.parseFloat();
}

  // half-period in ms for each h-bridge state
  high_state_duration = (unsigned long)(500000.0 / userfrq);

  // Serial.println("Enter in-line resistor value: ");
  // while (!Serial.available());

  // in_line = Serial.parseInt(); 
  // Serial.print("In-line resistance set to: ");
  // Serial.println(in_line);

  // Init timer1
  noInterrupts();   // disables global interrupts
  TCCR1A = 0;       // sets entire TCCR1A register to 0
  TCCR1B = 0;       // same for TCCR1B

  // Calculate OCR1A value
  float clockSpeed = 16000000.0; // Arduino clock speed in Hz
  float prescaler = 1024.0; // Prescaler value
  float tempOCR1A = clockSpeed / (prescaler * (2*userfrq)) - 1;

  unsigned long user_fq = static_cast<unsigned long>(round(tempOCR1A));

  if (user_fq < 1) {
      user_fq = 1; // Minimum practical value to avoid too fast interrupts
  } else if (user_fq > 65535) {
      user_fq = 65535; // Maximum value for a 16-bit timer
  }
  OCR1A = user_fq;    // 15624 = 16MHz / (1024 * 1Hz) - 1

  // Turns on CTC mode
  TCCR1B |= (1 << WGM12);

  // Sets CS10 and CS12 bits for 1024 prescaler
  TCCR1B |= (1 << CS10);
  TCCR1B |= (1 << CS12);

  // Enables timer compare IRQ
  TIMSK1 |= (1 << OCIE1A);

  interrupts();

//#ifdef DEBUG
//  unsigned long calculated_period = clockSpeed / (prescaler * (OCR1A + 1));
//  Serial.print("Calculated period: ");
//  Serial.print(calculated_period);
//  Serial.println(" Hz");
//  Serial.print("user_fq: ");
//  Serial.println(user_fq);
//  Serial.print("OCR1A Value: ");
//  Serial.println(OCR1A);
//#endif
}

void loop() {
  if (toggle_flag) {
    toggleHbridge();
    toggle_flag = false;
  }

  if (!readchk && L_state &&
      (micros() - high_state_start_time >= (unsigned long)(0.8 * high_state_duration))) {

    // optional sync pulse for NI acquisition
    digitalWrite(SYNC_PIN, HIGH);
    delayMicroseconds(20);
    digitalWrite(SYNC_PIN, LOW);

    readchk = true;
  }
}

// Timer1 ISR
ISR(TIMER1_COMPA_vect) {
  toggle_flag = true;
}

void toggleHbridge() {
  L_state = !L_state;

  if(L_state){
    readchk = false;
    digitalWrite(LOGIC1, HIGH);
    digitalWrite(LOGIC2, LOW);
    high_state_start_time = micros(); // Start timing the high state
  } else {
    digitalWrite(LOGIC1, LOW);
    digitalWrite(LOGIC2, HIGH);
  }
}

//float bigR(float drop, float sense, int in_l){

//  float i_calculated = drop/in_l;
//  float R = sense/i_calculated;

//  return R;
//}
